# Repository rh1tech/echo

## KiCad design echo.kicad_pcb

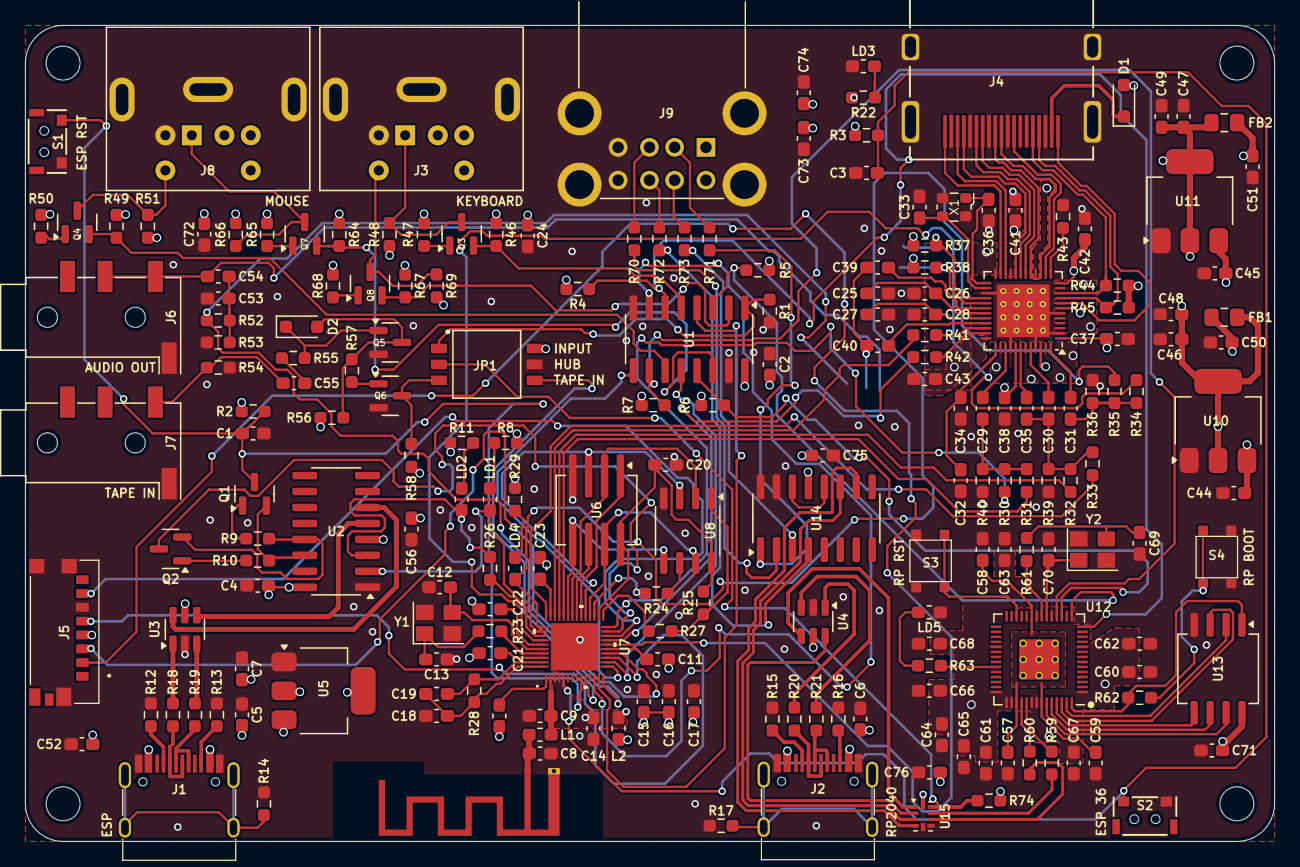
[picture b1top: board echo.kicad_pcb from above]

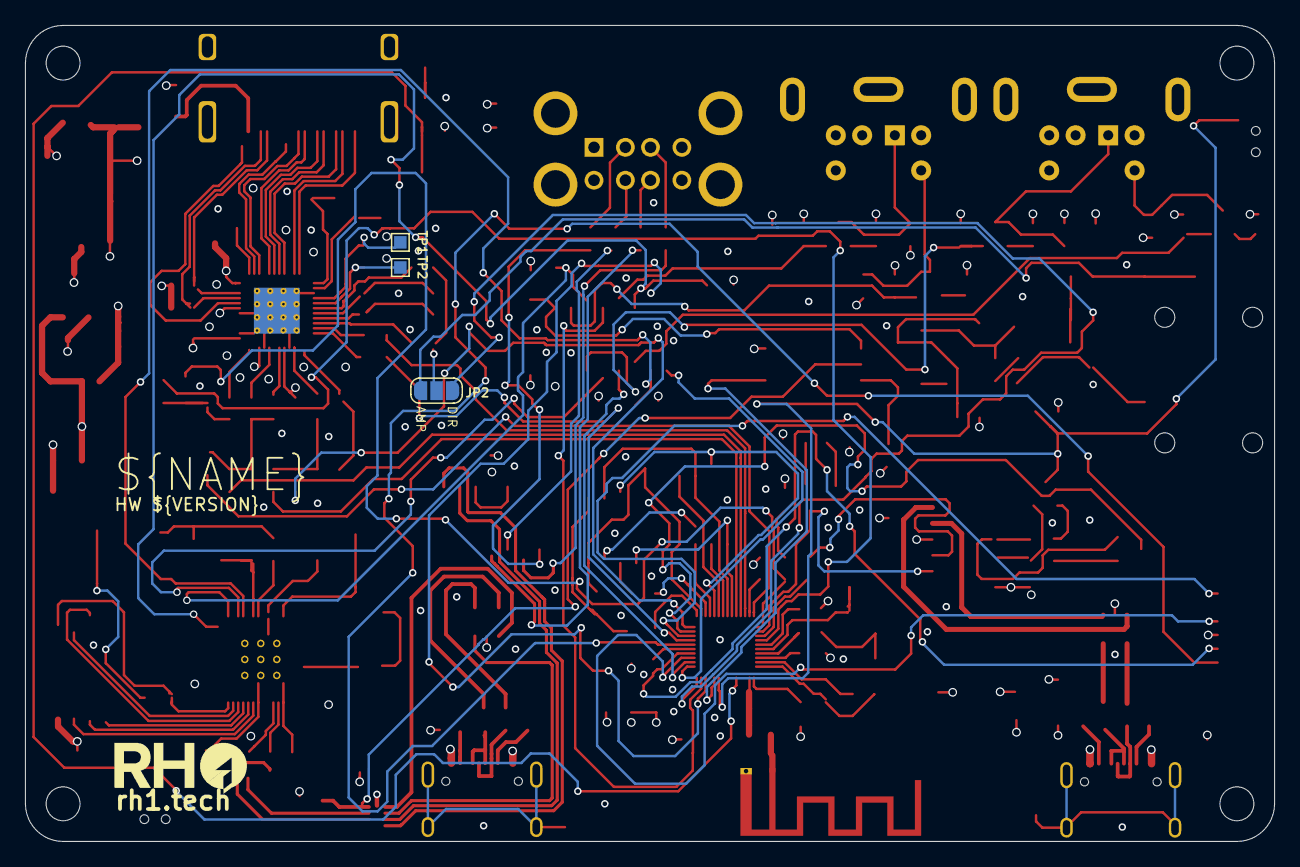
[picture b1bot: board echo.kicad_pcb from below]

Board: 4 copper layers, 99.5 x 65.0 mm, 209 parts (3 on the bottom side), 168 nets.

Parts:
AE1: Antenna_Shield; Antenna (2.4GHz)
C1, C3, C39, C40, C48, C49, C59, C61: 1u; Capacitor (0603)
C2, C4, C10, C11, C14, C15, C21, C22, C23, C24, C29, C30, C31, C37, C38, C41, C42, C43, C45, C52, C55, C56, C57, C58, C60, C62, C63, C64, C65, C66, C67, C68, C71, C72, C76: 100n; Capacitor (0603)
C5, C6, C7, C44, C46, C47, C50, C51, C54, C73, C74: 10u; Capacitor (0603)
C8: 2.4pF; Capacitor (0603)
C9: 1.5pF; Capacitor (0603)
C12, C13, C33, C36, C69, C70: 15p; Capacitor (0603)
C16: 10uF; Capacitor (0603)
C17, C20: 1uF; Capacitor (0603)
C18: 10nF; Capacitor (0603)
C19: 3.3nF; Capacitor (0603)
C25, C27, C32: 220n; Capacitor (0603)
C26, C28, C34, C75: 4.7u; Capacitor (0603)
C35: 1n; Capacitor (0603)
C53: 33n; Capacitor (0603)
D1: 1N5819WS; Diode (SOD-323)
D2: 1N4148; Diode (SOD-323)
FB1, FB2: 220R; Inductor (0805)
H1, H2, H3, H4: MountingHole; Mounting Hole (2.7mm)
J1, J2: USB4215-03-A; USB Type C
J3, J8: MDC-036; MiniDIN (6 Pin, female)
J4: DC3RX19JA2; HDMI (female)
J5: 0475710001; MicroSD (SMD, short)
J6, J7: PJ-320D; Jack (3.5mm, PJ-320D)
J9: SS-52100-004; USB Type A (stacked)
JP1: Main Jumpers; SW_DS05-127-2-03BK-SMT-TR
JP2: VGA AUDIO L; Jumper (solder, 3 pins)
L1: 3nH; Inductor (0603 1.05x0.95)
L2: 2.2nH; Inductor (0603 1.05x0.95)
LD1: Orange (TX); LED (0603)
LD2: Orange (RX); LED (0603)
LD3: Green; LED (0603)
LD4: Blue; LED (0603)
LD5: Blue (GPIO25); LED (0603)
Q1, Q2: BSS138; SOT-23
Q3, Q4, Q7, Q8: AO3400A; SOT-23
Q5, Q6: BC850; SOT-23
R1, R2, R3, R4, R5, R6, R7, R25, R55, R56, R57, R74: 10K; Resistor (0603)
R8, R11: 1.5K; Resistor (0603)
R9, R10: 2.2K; Resistor (0603)
R12, R13, R15, R16, R29: 5.1K; Resistor (0603)
R14, R17: 1M; Resistor (0603)
R18, R19, R20, R21, R70, R71, R72, R73: 22R; Resistor (0603)
R22, R43, R58, R61, R62, R63: 1K; Resistor (0603)
R23, R24, R27: 0R; Resistor (0603)
R26: 499R; Resistor (0603)
R28: 20K; Resistor (0603)
R30, R32, R34: 806R; Resistor (0603)
R31, R33, R35: 402R; Resistor (0603)
R36, R39, R40: 75R; Resistor (0603)
R37, R38, R47, R50, R65, R68: 4.7K; Resistor (0603)
R41, R42, R52, R54: 100R; Resistor (0603)
R44, R45: 2K; Resistor (0603)
R46, R48, R49, R51, R64, R66, R67, R69: 22K; Resistor (0603)
R53: 150R; Resistor (0603)
R59, R60: 27R; Resistor (0603)
S1: ESP Reset; TACT-SIDE-4623
S2: ESP Ctrl; TACT-SIDE-4623
S3: RP Reset; Button (SMD, 3x3mm, 1-1)
S4: RP Boot; Button (SMD, 3x3mm, 1-1)
TP1: MS9288_SCL; TestPoint (Pad 1.0x1.0mm)
TP2: MS9288_SDA; TestPoint (Pad 1.0x1.0mm)
U1: SN74CBT3257CDR; SOP-16
U2: CH340C; SOP-16
U3, U4: USBLC6-2SC6; SOT-23-6
U5: NCP1117 3.3; SOT-223
U6: W25Q32JVSIQ; SOIC-8 (Longer)
U7: ESP32-D0WD; QFN48_ESP32-D0WD-V3_EXP
U8: ESP-PSRAM32; SO-8
U9: MS9288A; QFN 48
U10: AMS1117-3.3; SOT-223
U11: AMS1117-1.8; SOT-223
U12: RP2040; QFN 56
U13: W25Q128JVSIQ; SOIC-8
U14: MW7211A; SOP-16
U15: TS3USB221RSER; UQFN-10
X1: 24.576 MHz; Crystal (2520)
Y1: 40 MHz; Crystal (3225)
Y2: 12 MHz; Crystal (3225)

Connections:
+3.3VP: C14.2, L2.1, U7.3 (VDD3P3), U7.4 (VDD3P3)
+3V3: C4.1, C7.1, C10.2, C11.2, C15.2, C16.2, C17.2, C21.2, C22.2, C23.2, C52.2, C56.1, C60.1, C61.1, C62.1, C63.1, C64.1, C65.1, C66.1, C67.1, C68.1, C71.1, C76.2, J5.P4 (VDD), L2.2, R2.2, R3.2, R4.2, R5.2, R6.2, R7.2, R8.2, R11.1, R22.2, R29.2, R46.1, R47.1, R49.1, R50.1, R56.1, R58.1, R64.1, R65.1, R67.1, R68.1, R74.1, U2.4 (3V), U2.16 (VCC), U5.2 (VO), U12.1 (IOVDD), U12.10 (IOVDD), U12.22 (IOVDD), U12.33 (IOVDD), U12.42 (IOVDD), U12.43 (ADC_AVDD), U12.44 (VREG_IN), U12.48 (USB_VDD), U12.49 (IOVDD), U13.8 (VCC), U15.10 (VCC)
/A_OUT: C54.1, J6.R, J6.T, JP2.3
/ESP32/ANT: AE1.1 (A), C8.1, L1.1
/ESP32/CAP1: C18.2, C19.2, R28.1, U7.48 (CAP1)
/ESP32/CAP2: C19.1, R28.2, U7.47 (CAP2)
/ESP32/SCK/CLK: U6.6 (CLK), U7.31 (SD_CLK)
/ESP32/SCS/CMD: U6.1 (~CS), U7.30 (SD_CMD)
/ESP32/SDI/SD1: U6.5 (DI(IO0)), U7.33 (SD_DATA_1), U8.5 (SI/SIO)
/ESP32/SDO/SD0: U6.2 (DO(IO1)), U7.32 (SD_DATA_0), U8.2 (SO/SIO)
/ESP32/SHD/SD2: U6.7 (IO3), U7.28 (SD_DATA_2), U8.7 (SIO3)
/ESP32/SWP/SD3: U6.3 (IO2), U7.29 (SD_DATA_3), U8.3 (SIO2)
/ESP32/VDD_SDIO: C20.2, R25.2, U6.8 (VCC), U7.26 (VDD_SDIO), U8.8 (VCC)
/ESP32/XIN: R23.1, U7.45 (XTAL_P)
/ESP32/XOUT: C12.1, U7.44 (XTAL_N), Y1.3
/ESP_EN: C1.1, Q1.3 (C), R2.1, S1.2, U7.9 (CHIP_PU)
/ESP_IO0: Q2.3 (C), U7.23 (GPIO0)
/ESP_IO1: LD2.1 (K), R26.2, U2.3 (RxD)
/ESP_IO2: J5.P7 (DAT0), U7.22 (GPIO2)
/ESP_IO3: LD1.1 (K), U2.2 (TxD), U7.40 (U0RXD)
/ESP_IO4: R30.1, U7.24 (GPIO4)
/ESP_IO5: R31.1, U7.34 (GPIO5)
/ESP_IO12: J5.P3 (CMD), U7.18 (MTDI)
/ESP_IO13: J5.P2 (CD/DAT3), U7.20 (MTCK)
/ESP_IO14: J5.P5 (CLK), U7.17 (MTMS)
/ESP_IO15: R42.1, U7.21 (MTDO)
/ESP_IO16: R25.1, R27.2, U8.1 (~CE)
/ESP_IO17: R24.2, U7.27 (GPIO17)
/ESP_IO18: R32.1, U7.35 (GPIO18)
/ESP_IO19: R33.1, U7.38 (GPIO19)
/ESP_IO21: R34.1, U7.42 (GPIO21)
/ESP_IO22: LD4.1 (K), R35.1, U7.39 (GPIO22)
/ESP_IO23: R41.1, U7.36 (GPIO23)
/ESP_IO25: JP2.1, R52.1, U7.14 (GPIO25)
/ESP_IO26: U1.9 (3A), U7.15 (GPIO26)
/ESP_IO27: U1.12 (4A), U7.16 (GPIO27)
/ESP_IO32: U1.7 (2A), U7.12 (32K_XP)
/ESP_IO33: U1.4 (1A), U7.13 (32K_XN)
/ESP_IO34: JP1.4, U7.10 (VDET_1)
/ESP_IO36: C3.1, R3.1, S2.2, U7.5 (SENSOR_VP)
/GPIO11: R4.1, U1.6 (2B2), U12.14 (GPIO11)
/GPIO12: R5.1, U1.3 (1B2), U12.15 (GPIO12)
/GPIO14: R6.1, U1.13 (4B2), U12.17 (GPIO14)
/GPIO15: R7.1, U1.10 (3B2), U12.18 (GPIO15)
/KB_CLK: J3.5, Q8.3 (D), R69.2
/KB_CLK_3V: Q8.2 (S), R67.2, U1.2 (1B1)
/KB_DATA: J3.1, Q3.3 (D), R48.2
/KB_DATA_3V: Q3.2 (S), R46.2, U1.5 (2B1)
/MS_CLK: J8.5, Q4.3 (D), R51.2
/MS_CLK_3V: Q4.2 (S), R49.2, U1.11 (3B1)
/MS_DATA: J8.1, Q7.3 (D), R66.2
/MS_DATA_3V: Q7.2 (S), R64.2, U1.14 (4B1)
/RP2040/GPIO25: R63.2, U12.37 (GPIO25)
/RP2040/QSPI_SCLK: U12.52 (QSPI_SCLK), U13.6 (CLK)
/RP2040/QSPI_SD0: U12.53 (QSPI_SD0), U13.5 (DI(IO0))
/RP2040/QSPI_SD1: U12.55 (QSPI_SD1), U13.2 (DO(IO1))
/RP2040/QSPI_SD2: U12.54 (QSPI_SD2), U13.3 (IO2)
/RP2040/QSPI_SD3: U12.51 (QSPI_SD3), U13.7 (IO3)
/RP2040/QSPI_SS: R62.1, U12.56 (QSPI_SS), U13.1 (~CS)
/RP2040/XIN: C70.1, U12.20 (XIN), Y2.1
/RP2040/XOUT: R61.1, U12.21 (XOUT)
/RP_D+: R59.1, U15.8 (D+)
/RP_D-: R60.1, U15.7 (D-)
/RUN: S3.1, U12.26 (RUN)
/SN74_S: JP1.1, R1.2, U1.1 (S)
/TAPE_IN: JP1.3, Q6.3 (C), R58.2
/TC1_D+: U2.5 (D+), U3.4 (I/O2)
/TC1_D-: U2.6 (D-), U3.6 (I/O1)
/TC2_D+: U4.4 (I/O2), U15.1 (1D+)
/TC2_D-: U4.6 (I/O1), U15.2 (1D-)
/UH_D+: U14.11 (DPU), U15.3 (2D+)
/UH_D-: U14.10 (DMU), U15.4 (2D-)
/UMSW: JP1.2, R74.2, U15.9 (S)
/USB Hub/D1+: R70.1, U14.2 (DP0)
/USB Hub/D1-: R71.1, U14.1 (DM0)
/USB Hub/D2+: R72.1, U14.4 (DP1)
/USB Hub/D2-: R73.1, U14.3 (DM1)
/VGA/ALIN: C39.1, U9.30 (ALIN)
/VGA/AMS_1V8: C41.1, C47.1, C49.1, FB2.1, U9.7 (AVDD18), U9.16 (AVDD18), U9.21 (AVDD18), U11.2 (VO)
/VGA/AMS_1V8A: C37.1, C38.1, C51.1, FB2.2, U9.1 (AVDD18_ADC), U9.41 (AVDD18_ADC), U9.46 (AVDD18_ADC)
/VGA/AMS_3V3: C43.1, C46.1, C48.1, FB1.2, U9.5 (DVDD33), U9.11 (DVDD33), U9.24 (DVDD33), U9.36 (DVDD33), U10.2 (VO)
/VGA/AMS_3V3A: C42.1, C50.1, FB1.1, U9.12 (AVDD33), U9.38 (AVDD33), U9.43 (AVDD33), U9.47 (AVDD33)
/VGA/ARIN: C40.1, U9.33 (ARIN)
/VGA/B: C29.1, U9.39 (B/Pb)
/VGA/DCCSCL: J4.15 (SCL), R44.1, U9.10 (DCCSCL)
/VGA/DDCSDA: J4.16 (SDA), R45.1, U9.9 (DDCSDA)
/VGA/G: C30.1, U9.44 (G/Y)
/VGA/HPDT: J4.19 (HOT_PLUG_DET), U9.8 (HotPlugDetect)
/VGA/R: C31.1, U9.48 (R/Pr)
/VGA/SCL: R37.1, TP1.1, U9.28 (SCL)
/VGA/SDA: R38.1, TP2.1, U9.29 (SDA)
/VGA/SOG_G: C30.2, C35.2, R32.2, R33.2, R39.1
/VGA/TMDS_CLK+: J4.10 (CLKP), U9.15 (TMDS_CLK+)
/VGA/TMDS_CLK-: J4.12 (CLKN), U9.14 (TMDS_CLK-)
/VGA/TMDS_D0+: J4.7 (D0P), U9.18 (TMDS-D0+)
/VGA/TMDS_D0-: J4.9 (D0N), U9.17 (TMDS_D0-)
/VGA/TMDS_D1+: J4.4 (D1P), U9.20 (TMDS_D1+)
/VGA/TMDS_D1-: J4.6 (D1N), U9.19 (TMDS_D1-)
/VGA/TMDS_D2+: J4.1 (D2P), U9.23 (TMDS_D2+)
/VGA/TMDS_D2-: J4.3 (D2N), U9.22 (TMDS_D2-)
/VGA_AIN: C39.2, C40.2, JP2.2
GND: AE1.2 (Shield), C1.2, C2.1, C3.2, C4.2, C5.2, C6.2, C7.2, C8.2, C9.2, C12.2, C13.2, C14.1, C15.1, C16.1, C17.1, C18.1, C20.1, C24.2, C25.2, C26.2, C27.2, C28.2, C32.2, C33.2, C34.2, C36.2, C37.2, C38.2, C41.2, C42.2, C43.2, C44.2, C45.2, C46.2, C47.2, C48.2, C49.2, C50.2, C51.2, C52.1, C53.1, C56.2, C57.2, C58.2, C59.2, C60.2, C61.2, C62.2, C63.2, C64.2, C65.2, C66.2, C67.2, C68.2, C69.2, C70.2, C71.2, C72.2, C73.2, C74.2, C75.2, C76.1, J1.1 (GND), J1.12 (GND), J2.1 (GND), J2.12 (GND), J3.3, J4.2 (G_D2), J4.5 (G_D1), J4.8 (G_D0), J4.11 (G_CLK), J4.17 (G_DDC/CEC), J4.20 (SHIELD1), J4.21 (SHIELD2), J4.22 (SHIELD3), J4.23 (SHIELD4), J5.G1 (GND_1), J5.G2 (GND_2), J5.G3 (GND_3), J5.P6 (VSS), J6.S, J7.S, J8.3, J9.4 (GND1), J9.8 (GND2), J9.9 (Shield), JP1.5, LD3.1 (K), LD5.1 (K), Q5.2 (E), Q6.2 (E), R1.1, R12.1, R13.1, R14.2, R15.1, R16.1, R17.2, R36.2, R39.2, R40.2, R43.1, R53.1, R54.2, S1.1, S2.1, S3.2, S4.2, U1.8 (GND), U1.15 (~OE), U2.1 (GND), U3.2 (GND), U4.2 (GND), U5.1 (GND), U6.4 (GND), U7.49 (GND), U8.4 (VSS), U9.2 (GND), U9.6 (GND), U9.27 (GND), U9.40 (GND), U9.45 (GND), U9.49 (EP), U10.1 (GND), U11.1 (GND), U12.19 (TESTEN), U12.57 (GND), U13.4 (GND), U14.15 (GND), U14.16 (GND), U15.5 (GND), U15.6 (~OE), X1.2 (GND), X1.4 (GND), Y1.2, Y1.4, Y2.2, Y2.4
unnamed: C10.1, U7.1 (VDDA)
unnamed: C13.1, R23.2, Y1.1
unnamed: C21.1, U7.46 (VDDA)
unnamed: C22.1, U7.43 (VDDA)
unnamed: C29.2, R30.2, R31.2, R40.1
unnamed: C31.2, R34.2, R35.2, R36.1
unnamed: C53.2, C54.2, R52.2, R53.2
unnamed: C55.1, J7.T, R54.1
unnamed: C55.2, R55.1
unnamed: C69.1, R61.2, Y2.3
unnamed: D1.1 (K), J4.18 (+5V)
unnamed: D2.2 (A), Q5.3 (C), R56.2, R57.1
unnamed: D2.1 (K), Q5.1 (B), R55.2
unnamed: J1.4 (CC1), R12.2
unnamed: J1.10 (CC2), R13.2
unnamed: J1.5 (DN2), J1.7 (DN1), R18.2
unnamed: J1.6 (DP1), J1.8 (DP2), R19.2
unnamed: J1.13 (SHIELD), R14.1
unnamed: J2.4 (CC1), R15.2
unnamed: J2.10 (CC2), R16.2
unnamed: J2.5 (DN2), J2.7 (DN1), R20.2
unnamed: J2.6 (DP1), J2.8 (DP2), R21.2
unnamed: J2.13 (SHIELD), R17.1
unnamed: J9.3 (D1+), R70.2
unnamed: J9.2 (D1-), R71.2
unnamed: J9.7 (D2+), R72.2
unnamed: J9.6 (D2-), R73.2
unnamed: LD1.2 (A), R8.1
unnamed: LD2.2 (A), R11.2
unnamed: LD3.2 (A), R22.1
unnamed: LD4.2 (A), R29.1
unnamed: LD5.2 (A), R63.1
unnamed: Q1.1 (B), R9.1
unnamed: Q1.2 (E), R10.2, U2.14 (RTS)
unnamed: Q2.1 (B), R10.1
unnamed: Q2.2 (E), R9.2, U2.13 (DTR)
unnamed: Q3.1 (G), R47.2
unnamed: Q4.1 (G), R50.2
unnamed: Q6.1 (B), R57.2
unnamed: Q7.1 (G), R65.2
unnamed: Q8.1 (G), R68.2
unnamed: R18.1, U3.1 (I/O1)
unnamed: R19.1, U3.3 (I/O2)
unnamed: R20.1, U4.1 (I/O1)
unnamed: R21.1, U4.3 (I/O2)
unnamed: R62.2, S4.1
unnamed: R27.1, U7.25 (GPIO16)
unnamed: C9.1, L1.2, U7.2 (LNA_IN)
unnamed: R26.1, U7.41 (U0TXD)
unnamed: C23.1, U7.37 (VDD3P3_CPU)
unnamed: C11.1, U7.19 (VDD3P3_RTC)
unnamed: R24.1, U8.6 (SCLK)
unnamed: R41.2, U9.34 (HSIN)
unnamed: C32.1, C34.1, U9.37 (REFP)
unnamed: C25.1, C26.1, U9.31 (REFQ0)
unnamed: C27.1, C28.1, U9.32 (REFQ1)
unnamed: C35.1, U9.42 (SOG/Y)
unnamed: R43.2, U9.13 (SWREF1k)
unnamed: R42.2, U9.35 (VSIN)
unnamed: C36.1, U9.25 (XTI), X1.1 (OSC)
unnamed: C33.1, U9.26 (XTO), X1.3 (OSC)
unnamed: R60.2, U12.46 (USB_DM)
unnamed: R59.2, U12.47 (USB_DP)
unnamed: C57.1, C58.1, C59.1, U12.23 (DVDD), U12.45 (VREG_VOUT), U12.50 (DVDD)
unnamed: U14.12 (VD33), U14.14 (VD3)
VBUS: C2.2, C5.1, C6.1, C24.1, C44.1, C45.1, C72.1, C73.1, C74.1, C75.1, D1.2 (A), J1.2 (VBUS), J1.11 (VBUS), J2.2 (VBUS), J2.11 (VBUS), J3.4, J8.4, J9.1 (VBUS1), J9.5 (VBUS2), JP1.6, R37.2, R38.2, R44.2, R45.2, R48.1, R51.1, R66.1, R69.1, U1.16 (VCC), U3.5 (VBUS), U4.5 (VBUS), U5.3 (VI), U10.3 (VI), U11.3 (VI), U14.13 (VDD5)

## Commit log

2025-04-30 Work-in-progress
2025-04-30 HW Revision 1.00
2025-04-30 Minor updates
2025-05-23 1.01 WIP
2025-05-23 Echo HW Rev 1.01
2025-06-24 Minor fixes
2025-07-19 HW Rev 1.03
2025-08-08 HW 1.04
2025-08-08 Removed unused files
2025-08-31 Rev 1.05 WIP
2025-09-01 1.05 WIP
2025-09-01 HW Revision 1.05
2025-09-23 HW 1.05
2025-09-24 HW 1.06 WIP
2025-09-26 Case added for 1.05
2025-09-26 1.06 WIP
2025-09-26 Echo HW 1.06 Release
